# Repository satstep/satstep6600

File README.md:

<h1 style="font-family: courier;" align="center"> satstep6600</h1>
<p align="center">

<div align="center"><i>An open source & fabbable stepper driver based on TB6600.</i></div>
</p>

satstep6600
--

satstep6600 is a **low cost and fabbable** stepper driver. Inspired by the [PiBot TB6600 stepper driver](http://reprap.org/wiki/PiBot_TB6600_Stepper_Driver), satstep6600 is designed on purpose to maintain all the high power specs while being safe to be operated and easy to build, even using the stardard Fab Lab equipment.

satstep6600 features:

- chopper type stepper motor driver
- 5A peak output current, **4.5A** sustained maximum (over 2A a fan is recommended)
- 8-40V input voltage 
- 1/1, 1/2A(0-71-100%), 1/2B(0-100%), 1/4, 1/8, 1/16 stepping modes
- suitable for NEMA 17, NEMA 23 and few NEMA 34 stepper motors
- thermal shut down protection
- under voltage lock out protection
- over-current detection protection
- optoisolated for all the inputs
- 4 x M3 fixing holes
- board size of 70x63mm
- it costs **13 euro**

Getting started
--

To connect your satstep6600 have a look to its **pinout**:

and connect the pin as follows:

- **VCC** -> to the VCC of the power supply, supported voltage between 8-40V
- **GND** on top -> to the GND of the power supply
- **GND** on bottom right -> to the GND of your controller board (eg a [satshakit](https://github.com/satshakit/) or an Arduino)
- **DIR** -> to the direction pin of your controller board, this defines the direction of the rotation
- **CLK** -> to the CLK pin of your controller board, this is used to receive the signals to makes steps
- **EN** -> to a pin with digital signal of your controller board, LOW means ENABLED

To configure the driver you can use the 5 position dip switch and the trimmer. The trimmer will regulate the amount of current given to the motor. Please make sure that you will **never supply more current** than the amount in the datasheet of your stepper motor. **Rotating the trimmer towards 103 will increase the current.** For continous use over 2A is recommended to use a fan to cool down the driver. 

The dip swith will change other settings as the following list:
- **TQ on**: 100% input Vref, **TQ off**: 30% input Vref
- **LATCH on**: thermal shutdown and over current protection, **LATCH off**: only thermal shutdown
- **M1, M2, M3** define the stepping mode:
	- M1 off, M2 off, M3 off -> standby
	- M1 off, M2 off, M3 on -> 1/1
	- M1 off, M2 on, M3 off -> 1/2A (0-71-100%)
	- M1 off, M2 on, M3 on -> 1/2B
	- M1 on, M2 off, M3 off -> 1/4
	- M1 on, M2 off, M3 on -> 1/8
	- M1 on, M2 on, M3 off -> 1/16

Downloads
--

**downloads (right click, download as)**

- [satstep6600 board](https://github.com/satstep/satstep6600/raw/master/eagle/satstep6600.brd)
- [satstep6600 schematic](https://github.com/satstep/satstep6600/raw/master/eagle/satstep6600.sch)
- [satstep6600 top internal path png](https://github.com/satstep/satstep6600/raw/master/media/top_internal.png)
- [satstep6600 top external path png](https://github.com/satstep/satstep6600/raw/master/media/top_external.png)
- [satstep6600 bottom internal path png](https://github.com/satstep/satstep6600/raw/master/media/bottom_internal.png)
- [satstep6600 bottom external path png](https://github.com/satstep/satstep6600/raw/master/media/bottom_external.png)
- [satstep6600 board for 0.4 mills](https://github.com/satstep/satstep6600/raw/master/eagle/satstep6600_04/satstep6600.brd)
- [satstep6600 schematic for 0.4 mills](https://github.com/satstep/satstep6600/raw/master/eagle/satstep6600_04/satstep6600.sch)
- [satstep6600 for 0.4 mills top internal path png](https://github.com/satstep/satstep6600/raw/master/media/satstep6600_04/top_internal.png)
- [satstep6600 for 0.4 mills top external path png](https://github.com/satstep/satstep6600/raw/master/media/satstep6600_04/top_external.png)
- [satstep6600 for 0.4 mills bottom internal path png](https://github.com/satstep/satstep6600/raw/master/media/satstep6600_04/bottom_internal.png)
- [satstep6600 for 0.4 mills bottom external path png](https://github.com/satstep/satstep6600/raw/master/media/satstep6600_04/bottom_external.png)
- [satstep6600 BOM ods](https://github.com/satstep/satstep6600/raw/master/docs/satstep6600_BOM.ods)
- [satstep6600 BOM xlsx](https://github.com/satstep/satstep6600/raw/master/docs/satstep6600_BOM.xlsx)

Media
--

videos of satstep6600 moving NEMA 23 stepper motors:

other images of the satstep6600 driver board:

What's in the repo
--

- **[docs](https://github.com/satstep/satstep6600/tree/master/docs)**: BOM files
- **[egle](https://github.com/satstep/satstep6600/tree/master/eagle)**: eagle projects of the satstep6600 drive
- **[media](https://github.com/satstep/satstep6600/tree/master/media)**: svgs, connections schemas, images for cnc milling machine, other images

Authors
--

- Daniele Ingrassia

Contact
--

- **ingrassiada@gmail.com**
- **[linkedin](http://it.linkedin.com/in/danieleingrassia)**

Thanks
--

[Fablab Kamp-Lintfort](http://fablab.hochschule-rhein-waal.de/index.php/de/)<br />
Hochschule Rhein-Waal<br />
Friedrich-Heinrich-Allee 25, 47475 Kamp-Lintfort, Germany<br />
fablab@hochschule-rhein-waal.de

License
--

This work is licensed under the terms of the open source license: Creative Commons Attribution-ShareAlike 4.0 International ([CC BY-SA 4.0](https://creativecommons.org/licenses/by-sa/4.0/)).

Disclaimer  
--

<div class="align-justify">
This hardware/software is provided "as is", and you use the hardware/software at your own risk. Under no circumstances shall any author be liable for direct, indirect, special, incidental, or consequential damages resulting from the use, misuse, or inability to use this hardware/software, even if the authors have been advised of the possibility of such damages.</div>

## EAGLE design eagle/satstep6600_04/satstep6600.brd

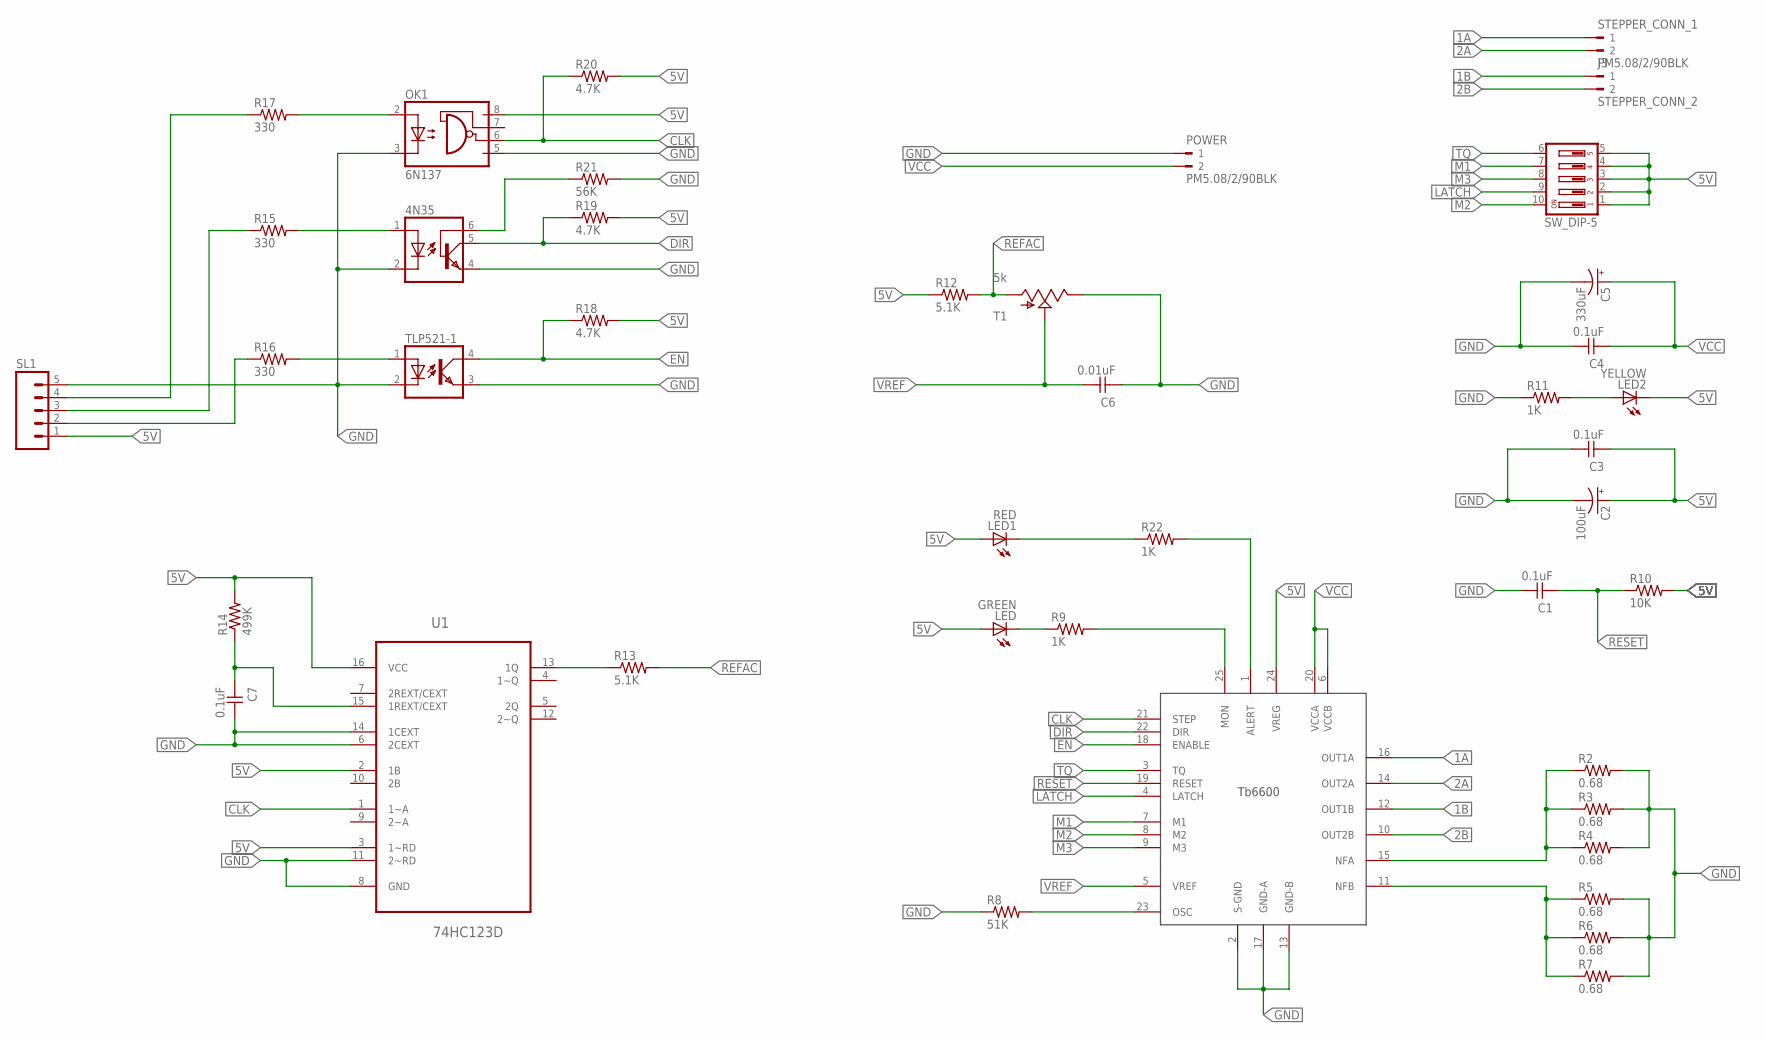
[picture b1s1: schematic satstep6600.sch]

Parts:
4N35: 4N35; DIL06
C1, C3, C4, C7: 0.1uF; 1206
C2: 100uF; PANASONIC_C
C5: 330uF; CPOL-RADIAL-1000UF-63V
C6: 0.01uF; 1206
J3: STEPPER_CONN_2; WEIDMULLER_PM5.08_2
LED: GREEN; 1206
LED1: RED; 1206
LED2: YELLOW; 1206
OK1: 6N137; DIL08
POWER: PM5.08/2/90BLK; WEIDMULLER_PM5.08_2
R2, R3, R4, R5, R6, R7: 0.68; 2512
R8: 51K; R1206
R9, R11, R22: 1K; R1206
R10: 10K; R1206
R12, R13: 5.1K; R1206
R14: 499K; R1206
R15, R16, R17: 330; R1206
R18, R19, R20: 4.7K; R1206
R21: 56K; R1206
SL1: M05; 05P
STEPPER_CONN_1: PM5.08/2/90BLK; WEIDMULLER_PM5.08_2
SW_DIP-5: SD4-05
T1: 5k; TS53YL104MR10_TRIMMER
TLP521-1: PC817; DIL04
U1: 74HC123D; SOIC127P600X175-16N
U$1: TB6600HG; P-HZIP25-1.00G

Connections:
1A: STEPPER_CONN_1.1, U$1.16 (OUT1A)
1B: J3.1, U$1.12 (OUT1B)
2A: STEPPER_CONN_1.2, U$1.14 (OUT2A)
2B: J3.2, U$1.10 (OUT2B)
5V: C2.+, C3.1, LED.1 (A), LED1.1 (A), LED2.2 (C), OK1.8 (VCC), R10.2, R12.1, R14.2, R18.2, R19.2, R20.2, SL1.1, SW_DIP-5.1, SW_DIP-5.2, SW_DIP-5.3, SW_DIP-5.4, SW_DIP-5.5, U1.2 (1B), U1.3 (1~RD), U1.16 (VCC), U$1.24 (VREG)
ALERT: R22.2, U$1.1 (ALERT)
CLK: OK1.6 (VO), R20.1, U1.1 (1~A), U$1.21 (STEP)
DIR: 4N35.5 (COL), R19.1, U$1.22 (DIR)
EN: R18.1, TLP521-1.4 (COL), U$1.18 (ENABLE)
GND: 4N35.2 (C), 4N35.4 (EMI), C1.2, C2.-, C3.2, C4.2, C5.2 (-), C6.1, C7.2, OK1.3 (C), OK1.5 (GND), POWER.1, R2.2, R3.2, R4.2, R5.2, R6.2, R7.2, R8.1, R11.1, R21.2, SL1.5, T1.P$2 (E), TLP521-1.2 (C), TLP521-1.3 (EMIT), U1.6 (2CEXT), U1.8 (GND), U1.11 (2~RD), U1.14 (1CEXT), U$1.2 (S-GND), U$1.13 (GND-B), U$1.17 (GND-A)
LATCH: SW_DIP-5.9, U$1.4 (LATCH)
M1: SW_DIP-5.7, U$1.7 (M1)
M2: SW_DIP-5.10, U$1.8 (M2)
M3: SW_DIP-5.8, U$1.9 (M3)
unnamed: R5.1, R6.1, R7.1, U$1.11 (NFB)
unnamed: R8.2, U$1.23 (OSC)
unnamed: LED.2 (C), R9.1
unnamed: R2.1, R3.1, R4.1, U$1.15 (NFA)
unnamed: LED1.2 (C), R22.1
unnamed: LED2.1 (A), R11.2
unnamed: R13.1, U1.13 (1Q)
unnamed: C7.1, R14.1, U1.15 (1REXT/CEXT)
unnamed: R16.2, TLP521-1.1 (A)
unnamed: 4N35.1 (A), R15.2
unnamed: OK1.2 (A), R17.2
unnamed: 4N35.6 (BAS), R21.1
unnamed: R16.1, SL1.2
unnamed: R15.1, SL1.3
unnamed: R17.1, SL1.4
unnamed: R9.2, U$1.25 (MON)
REFAC: R12.2, R13.2, T1.P$3 (A)
RESET: C1.1, R10.1, U$1.19 (RESET)
TQ: SW_DIP-5.6, U$1.3 (TQ)
VCC: C4.1, C5.1 (+), POWER.2, U$1.6 (VCCB), U$1.20 (VCCA)
VREF: C6.2, T1.P$1 (S), U$1.5 (VREF)

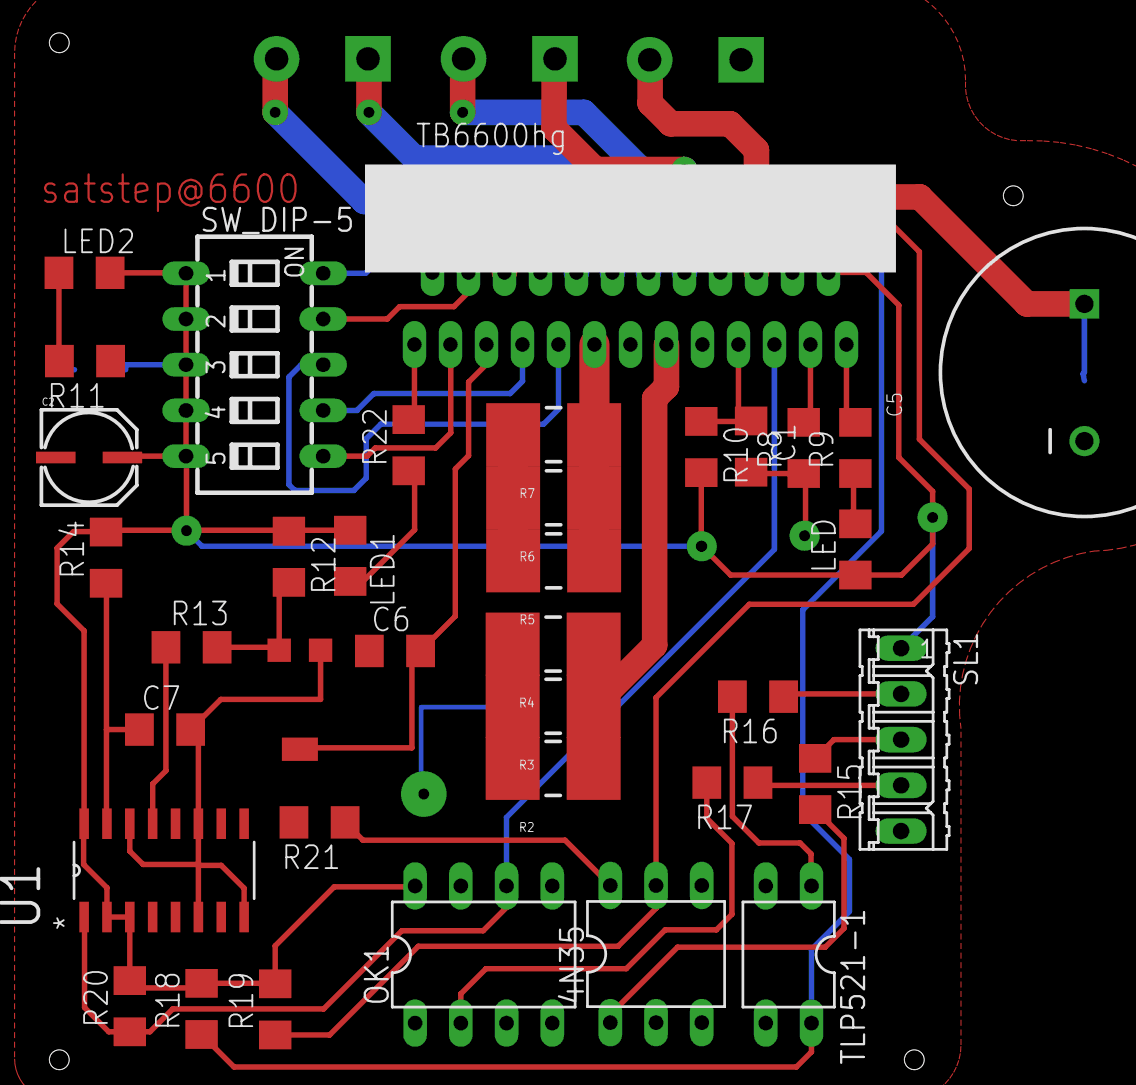
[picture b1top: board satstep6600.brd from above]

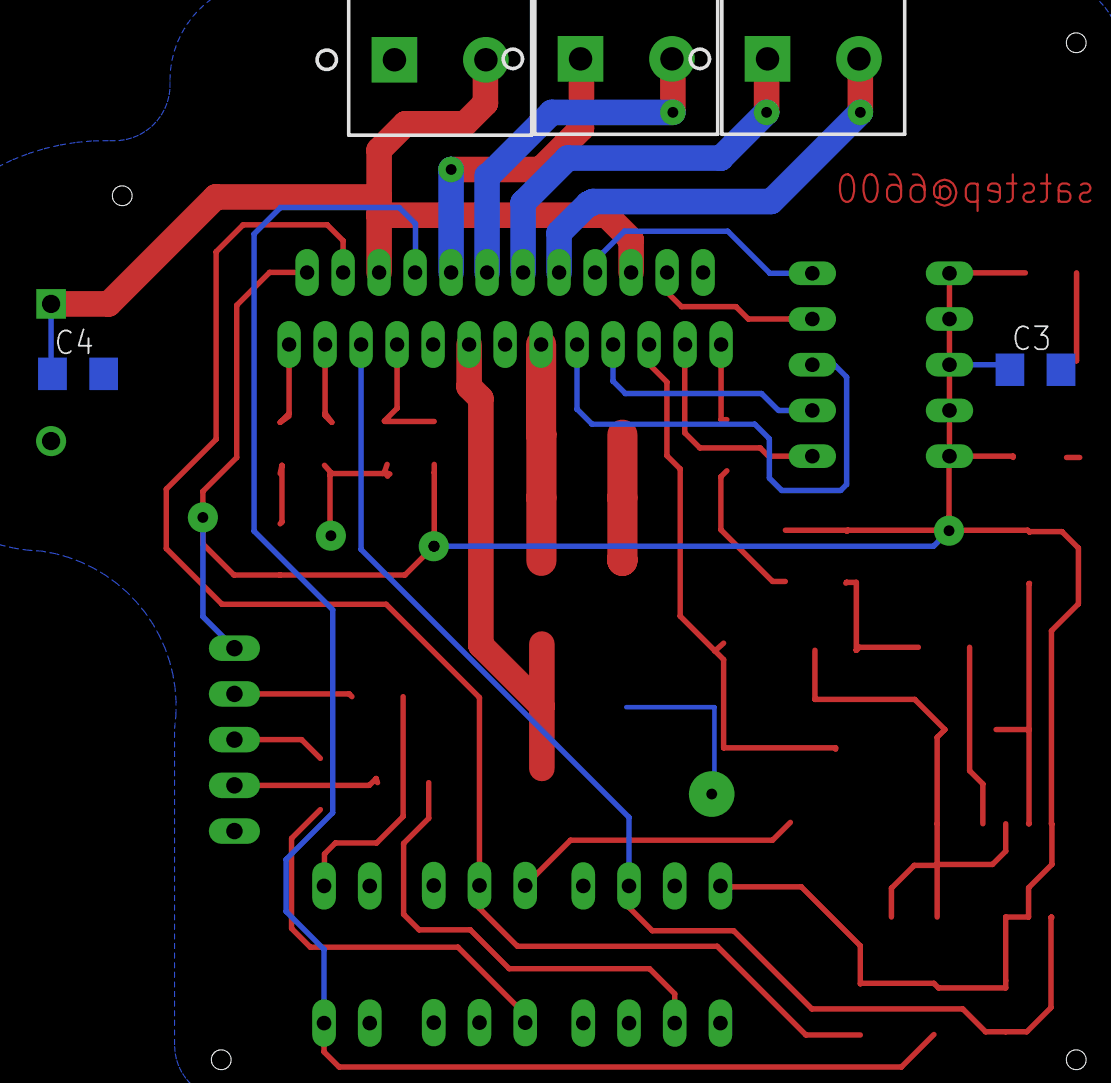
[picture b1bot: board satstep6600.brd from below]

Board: 2 copper layers, 42 parts (5 on the bottom side), 35 nets.

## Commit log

2017-01-22 added license and basic readme
2017-01-22 added eagle files and images of the pcbs
2017-01-22 fixed links on the repo
2017-01-22 added BOM
2017-01-22 added links and cleaned eagle files
2017-01-22 added info on the readme and made the pinout
2017-01-22 added info on the readme
2017-01-22 addedd media
2017-01-22 added media
2017-01-22 fixed links to the videos
2017-01-22 organized the media section
2017-01-22 added cooling info
2017-01-22 added bolds
2017-01-24 renamed eagle files according to the given name of the driver
2017-01-24 added recommendation on the fan
2017-01-24 fixed grammar error
2017-01-27 added new version for 0.4mm mills and resized all the pngs
2017-01-27 fixed links
2018-04-15 mod the trimmmer value
2018-04-15 safier trimmer value
2018-04-15 safer trimmer value
2018-06-19 fixed pinout
2019-12-26 license change

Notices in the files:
parts and their libraries:
SparkFun-Resistors: Licensing: Creative Commons ShareAlike 4.0 International - https://creativecommons.org/licenses/by-sa/4.0
